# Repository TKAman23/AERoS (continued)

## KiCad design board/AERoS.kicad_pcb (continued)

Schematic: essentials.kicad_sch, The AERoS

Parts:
C29: 100n; C_0402_1005Metric; MFR. Part # CL05B104KO5NNNC; JLCPCB Part # C1525
C30, C31: 30p; C_0402_1005Metric; MFR. Part # 0402CG300J500NT; JLCPCB Part # C1570
J8: Conn_01x03_Pin; PinHeader_1x03_P2.54mm_Vertical_SMD_Pin1Left; MFR. Part # DZ254S-11-03-48; JLCPCB Part # C5160786
R25: 50k; R_0402_1005Metric; MFR. Part # RTT025002FTH; JLCPCB Part # C166559
Y1: 16M; Crystal_SMD_3225-4Pin_3.2x2.5mm; MFR. Part # X322516MMB4SI; JLCPCB Part # C112972

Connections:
+3.3V: J8.1; also elsewhere on the board
/Microcontroller/Essentials/BOOT0: R25.1; also elsewhere on the board
/Microcontroller/Essentials/HSE_IN: C30.1, Y1.1; also elsewhere on the board
/Microcontroller/Essentials/HSE_OUT: C31.1, Y1.3; also elsewhere on the board
/Microcontroller/Essentials/NRST: C29.2; also elsewhere on the board
/Microcontroller/Essentials/SW_BOOT0: J8.2, R25.2
GND: C29.1, C30.2, C31.2, J8.3, Y1.2, Y1.4; also elsewhere on the board

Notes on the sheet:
Booting Circuit
Crystal Oscillator
STM32 Functional Circuits

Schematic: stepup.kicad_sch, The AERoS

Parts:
C8, C9: 100n; C_0402_1005Metric; MFR. Part # CL05B104KO5NNNC; JLCPCB Part # C1525
C10: 22n; C_0201_0603Metric; MFR. Part # 0201X223K160NT; JLCPCB Part # C285066
C11, C15, C16: 47u; C_1812_4532Metric; MFR. Part # C4532X5R1A476MT000N; JLCPCB Part # C342615
C12: 100u; C_2220_5750Metric; MFR. Part # C5750X5R1A107MT000E; JLCPCB Part # C76692
C13: 22u; C_1210_3225Metric; MFR. Part # CL32A226KAJNNNE; JLCPCB Part # C52306
C14: 4u7; C_0805_2012Metric; MFR. Part # CL21A475KAQNNNE; JLCPCB Part # C1779
C17: 1n; C_0402_1005Metric; MFR. Part # 0402B102K500NT; JLCPCB Part # C1523
L2: 1u; 0806; MFR. Part # BDHE002016081R0MQ1; JLCPCB Part # C702824
Q5: PMOS; DFN-6-2EP_(AGM20P16AS); MFR. Part # AGM20P16AS; JLCPCB Part # C18221388
R16: 121k; R_0402_1005Metric; MFR. Part # 0402WGF1213TCE; JLCPCB Part # C11693
R17: 536k; R_0402_1005Metric; MFR. Part # 0402WGF5363TCE; JLCPCB Part # C68457
R18: 300k; R_0402_1005Metric; MFR. Part # 0402WGF3003TCE; JLCPCB Part # C25774
R19: 44k2; R_0402_1005Metric; MFR. Part # 0402WGF4422TCE; JLCPCB Part # C25895
R20: 78k7; R_0402_1005Metric; MFR. Part # 0402WGF7872TCE; JLCPCB Part # C67239
U3: TPS611781RNWR; RNW0013A; MFR. Part # TPS611781RNWR; JLCPCB Part # C2862009
U4: MCP4552T-104E/MF; DFN8_3x3MC_MCH; MFR. Part # MCP4552T-104E/MF; JLCPCB Part # C623602

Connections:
+3.3V: U4.8 (VDD); also elsewhere on the board
/Microcontroller/SERVO_ON: U3.11 (EN); also elsewhere on the board
/Power/Battery Direct/BATT_OUT: C12.1, C13.1, L2.1, U3.12 (VIN); also elsewhere on the board
/Power/Servo Power/SERVO+: C11.1, C15.1, C16.1, Q5.3 (S), R17.2; also elsewhere on the board
/Power/Servo Power/Step-Up/PREPOT: R17.1, U3.5 (FB), U4.6 (P0B)
GND: C9.1, C11.2, C12.2, C13.2, C14.2, C15.2, C16.2, C17.2, R18.2, R20.2, U3.2 (AGND), U3.6 (PGND), U4.1 (HVC/A0), U4.4 (VSS), U4.5 (P0W), U4.7 (A1), U4.9 (EP); also elsewhere on the board
unnamed: C17.1, R19.2
unnamed: C9.2, C10.1, Q5.1 (D), R16.1, U3.8 (VOUT)
unnamed: C10.2, Q5.2 (G), R16.2, U3.9 (DISDRV)
unnamed: C8.2, U3.13 (BST)
unnamed: R19.1, U3.4 (COMP)
unnamed: R18.1, U3.1 (FREQ_SYNC)
unnamed: R20.1, U3.3 (ILIMIT)
unnamed: C8.1, L2.2, U3.7 (SW)
unnamed: C14.1, U3.10 (VCC)
SCL: U4.2 (SCL); also elsewhere on the board
SDA: U4.3 (SDA); also elsewhere on the board

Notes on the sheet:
6V at 78.7k ohms
Digipot
Servo Power Step-Up
Step-Up Regulator Circuit
I2C Address: 00

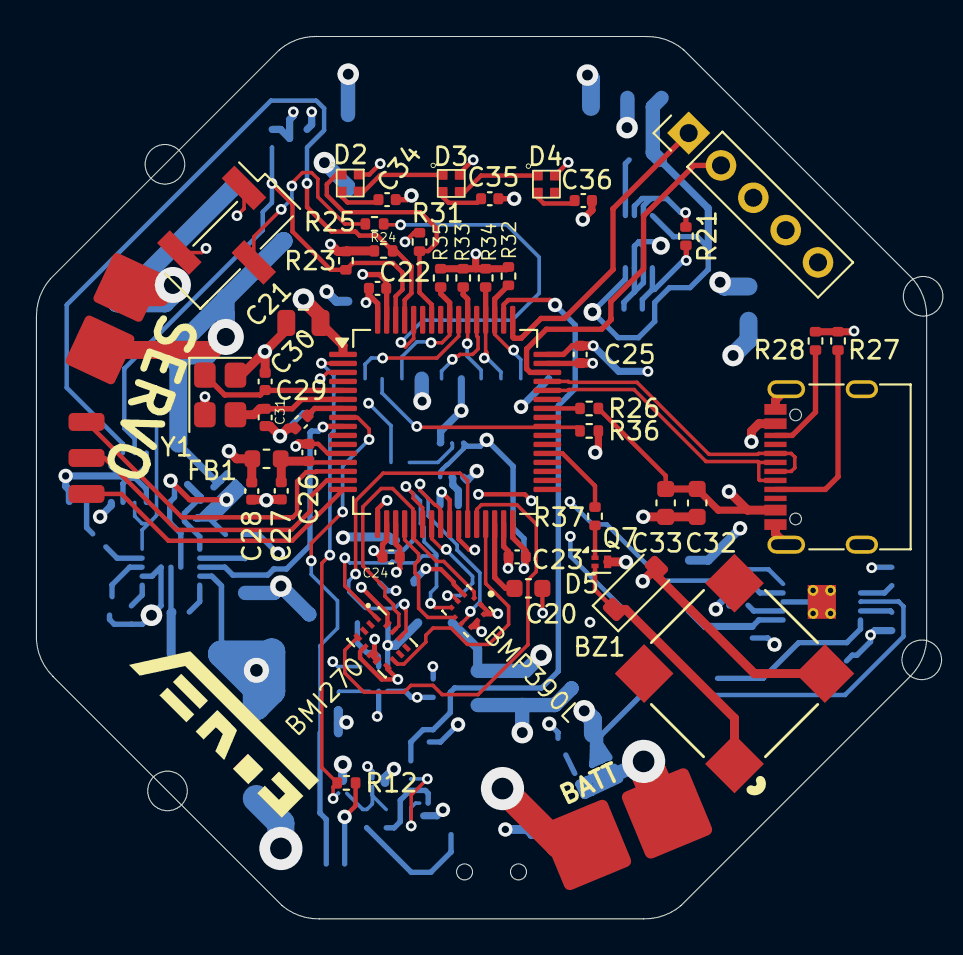
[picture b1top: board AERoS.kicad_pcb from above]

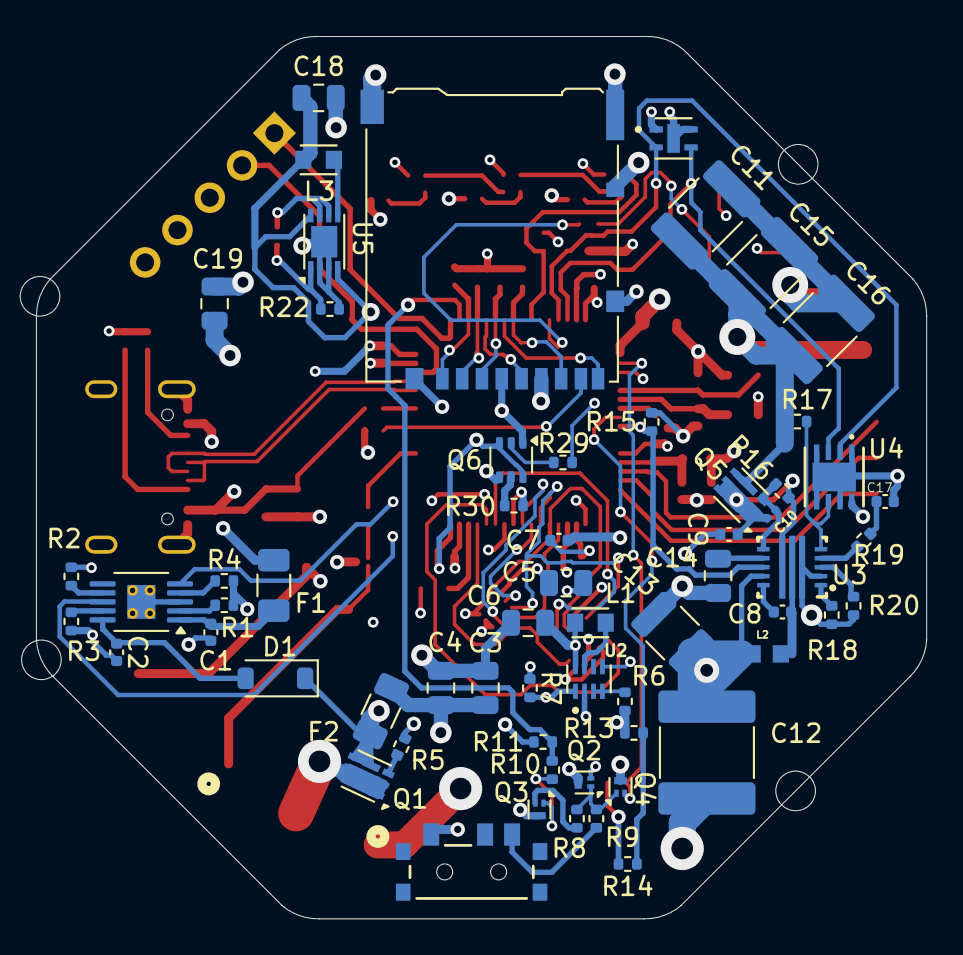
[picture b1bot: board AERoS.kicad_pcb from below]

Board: 4 copper layers, 49.5 x 49.0 mm, 118 parts (61 on the bottom side), 90 nets.

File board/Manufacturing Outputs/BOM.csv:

Comment,Designator,Footprint,JLCPCB Part #
MLT-8530,BZ1,CustomLibrary2:MLT-8530_JHE,C94599
1u,"C1,C2,C27,C28",Capacitor_SMD:C_0402_1005Metric,C14445
4u7,"C3,C4,C14,C18",Capacitor_SMD:C_0805_2012Metric,C1779
10u,"C5,C6,C19,C21",Capacitor_SMD:C_0805_2012Metric,C15850
100n,"C7,C8,C9,C22,C23,C24,C25,C29",Capacitor_SMD:C_0402_1005Metric,C1525
22n,C10,Capacitor_SMD:C_0201_0603Metric,C285066
47u,"C11,C15,C16",Capacitor_SMD:C_1812_4532Metric,C342615
100u,C12,Capacitor_SMD:C_2220_5750Metric,C76692
22u,C13,Capacitor_SMD:C_1210_3225Metric,C52306
1n,C17,Capacitor_SMD:C_0402_1005Metric,C1523
2u2,C20,Capacitor_SMD:C_0603_1608Metric,C23630
10n,C26,Capacitor_SMD:C_0402_1005Metric,C1524
30p,"C30,C31",Capacitor_SMD:C_0402_1005Metric,C1570
10u,C32,Capacitor_SMD:C_0603_1608Metric,C1691
4u7,C33,Capacitor_SMD:C_0603_1608Metric,C1705
220n,"C34,C35,C36",Capacitor_SMD:C_0402_1005Metric,C16772
SD101CW-E3-18,"D1,D5",Diode_SMD:D_SOD-123,C3313033
SK6805,"D2,D3,D4",CustomLibrary2:SK6805-EC15,C2890035
600m,F1,Fuse:Fuse_1206_3216Metric,C2154056
500m,F2,Fuse:Fuse_1206_3216Metric,C20798
GZ1608D121TF,FB1,Inductor_SMD:L_0603_1608Metric,C12391
MountingHole,"H1,H2,H3,H4",MountingHole:MountingHole_2.2mm_M2,
Conn_01x01_Pin,"J1,J2",CustomLibrary2:Pad_4x4mm,
Conn_01x01_Pin,"J3,J4",CustomLibrary2:Pad_3x3mm,
Conn_01x01_Pin,"J5,J6,J7",Connector_Wire:SolderWirePad_1x01_SMD_1x2mm,
Conn_01x03_Pin,J8,Connector_PinHeader_2.54mm:PinHeader_1x03_P2.54mm_Vertical_SMD_Pin1Left,C5160786
USB_C_Receptacle_USB2.0_14P,J9,Connector_USB:USB_C_Receptacle_G-Switch_GT-USB-7010ASV,C2988369
Conn_01x05_Pin,J10,Connector_PinHeader_2.54mm:PinHeader_1x05_P2.54mm_Vertical,
SD Card Hirose DM3AT,J11,Connector_Card:microSD_HC_Hirose_DM3AT-SF-PEJM5,C114218
2u2,"L1,L3",CustomLibrary2:IND_LQH2MPZ2R2MGRL,C2042050
1u,L2,CustomLibrary2:0806,C702824
PMOS,"Q1,Q5",CustomLibrary2:DFN-6-2EP_(AGM20P16AS),C18221388
NMOS,"Q2,Q3,Q4,Q7",CustomLibrary2:DFN-3(0.6x1),C20605534
NMOS,Q6,Package_TO_SOT_SMD:SOT-363_SC-70-6,C15215
1k,"R1,R5,R8,R9,R23,R24,R29,R30,R32,R33,R34,R35,R36",Resistor_SMD:R_0402_1005Metric,C11702
10k,"R2,R3,R31",Resistor_SMD:R_0402_1005Metric,C25744
1k5,R4,Resistor_SMD:R_0402_1005Metric,C25867
100k,"R6,R11,R12,R13,R15,R26",Resistor_SMD:R_0402_1005Metric,C25741
267k,R7,Resistor_SMD:R_0402_1005Metric,C270622
100,R10,Resistor_SMD:R_0402_1005Metric,C25076
365k,R14,Resistor_SMD:R_0402_1005Metric,C27006
121k,R16,Resistor_SMD:R_0402_1005Metric,C11693
536k,R17,Resistor_SMD:R_0402_1005Metric,C68457
300k,R18,Resistor_SMD:R_0402_1005Metric,C25774
44k2,R19,Resistor_SMD:R_0402_1005Metric,C25895
78k7,R20,Resistor_SMD:R_0402_1005Metric,C67239
976k,R21,Resistor_SMD:R_0402_1005Metric,C25802
562k,R22,Resistor_SMD:R_0402_1005Metric,C48838
50k,R25,Resistor_SMD:R_0402_1005Metric,C166559
5k1,"R27,R28",Resistor_SMD:R_0402_1005Metric,C25905
470,R37,Resistor_SMD:R_0402_1005Metric,C25117
SW_SPDT,SW1,CustomLibrary2:MK-12C02-G020_GSW,C963206
BQ24090DGQ,U1,Package_SO:HVSSOP-10-1EP_3x3mm_P0.5mm_EP1.57x1.88mm_ThermalVias,C43306
TPS62840DLCR,U2,CustomLibrary2:SON50P200X150X100-8N,C2071859
TPS611781RNWR,U3,Custom_Library:RNW0013A,C2862009
MCP4552T-104E/MF,U4,CustomLibrary2:DFN8_3x3MC_MCH,C623602
MCP1640x-xMC,U5,Package_DFN_QFN:DFN-8-1EP_3x2mm_P0.5mm_EP1.75x1.45mm,C623037
STM32F411RET6,U6,Package_QFP:LQFP-64_10x10mm_P0.5mm,C94355
BMI270,U7,Custom_Library:XDCR_BMI270,C2836813
BMP390L,U8,Custom_Library:XDCR_BMP390L,C2684802
SHTC3,U9,Custom_Library:SON100P200X200X80-5N,C194656
16M,Y1,Crystal:Crystal_SMD_3225-4Pin_3.2x2.5mm,C5452684

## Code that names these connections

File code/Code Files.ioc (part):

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Mcu.Name=STM32F411R(C-E)Tx
Mcu.Package=LQFP64
Mcu.UserName=STM32F411RETx
PA0-WKUP.GPIOParameters=GPIO_Label
PA0-WKUP.GPIO_Label=SERVO1
PA0-WKUP.Signal=S_TIM2_CH1_ETR
PA1.GPIOParameters=GPIO_Label
PA1.GPIO_Label=SERVO2
PA1.Signal=S_TIM2_CH2
PA10.Signal=GPIO_Analog
PA11.GPIOParameters=GPIO_Label
PA11.GPIO_Label=USB_D-
PA11.Mode=Device_Only
PA11.Signal=USB_OTG_FS_DM
PA12.GPIOParameters=GPIO_Label
PA12.GPIO_Label=USB_D+
PA12.Mode=Device_Only
PA12.Signal=USB_OTG_FS_DP
PA13.GPIOParameters=GPIO_Label
PA13.GPIO_Label=SW_DIO
PA13.Mode=Serial_Wire
PA13.Signal=SYS_JTMS-SWDIO
PA14.GPIOParameters=GPIO_Label
PA14.GPIO_Label=SW_CLK
PA14.Mode=Serial_Wire
PA14.Signal=SYS_JTCK-SWCLK
PA15.GPIOParameters=GPIO_Label
PA15.GPIO_Label=KEEP_ON
PA15.Signal=GPIO_Output
PA2.GPIOParameters=GPIO_Label
PA2.GPIO_Label=SERVO3
PA2.Signal=S_TIM2_CH3
PA3.Signal=GPIO_Analog
PA4.GPIOParameters=GPIO_Label
PA4.GPIO_Label=BMP_CS
PA4.Signal=GPIO_Output
PA5.GPIOParameters=GPIO_Label
PA5.GPIO_Label=CLK
PA5.Mode=Full_Duplex_Master
PA5.Signal=SPI1_SCK
PA6.GPIOParameters=GPIO_Label
PA6.GPIO_Label=MISO
PA6.Mode=Full_Duplex_Master
PA6.Signal=SPI1_MISO
PA7.GPIOParameters=GPIO_Label
PA7.GPIO_Label=MOSI
PA7.Mode=Full_Duplex_Master
PA7.Signal=SPI1_MOSI
PA8.Signal=GPIO_Analog
PA9.GPIOParameters=GPIO_Label
PA9.GPIO_Label=USB_SENSE
PA9.Mode=Activate_VBUS
PA9.Signal=USB_OTG_FS_VBUS
PB0.Signal=GPIO_Analog
PB1.GPIOParameters=GPIO_Label
PB1.GPIO_Label=IMU_CS
PB1.Signal=GPIO_Output
PB10.GPIOParameters=GPIO_Label
PB10.GPIO_Label=IMU_INT2
PB10.Signal=GPXTI10
PB12.Signal=GPIO_Analog
PB13.Signal=GPIO_Analog
PB14.Signal=GPIO_Analog
PB15.Signal=GPIO_Analog
PB2.GPIOParameters=GPIO_Label
PB2.GPIO_Label=IMU_INT1
PB2.Signal=GPXTI2
PB3.GPIOParameters=GPIO_Label
PB3.GPIO_Label=SD_SW
PB3.Signal=GPXTI3
PB4.GPIOParameters=GPIO_Label
PB4.GPIO_Label=DAT0
PB4.Mode=SD_4_bits_Wide_bus
PB4.Signal=SDIO_D0
PB5.GPIOParameters=GPIO_Label
PB5.GPIO_Label=CHG
PB5.Signal=GPXTI5
PB6.GPIOParameters=GPIO_Label
PB6.GPIO_Label=LED
PB6.Signal=S_TIM4_CH1
PB7.GPIOParameters=GPIO_Label
PB7.GPIO_Label=PG
PB7.Signal=GPXTI7
PB8.GPIOParameters=GPIO_Label
PB8.GPIO_Label=SCL
PB8.Mode=I2C
PB8.Signal=I2C1_SCL
PB9.GPIOParameters=GPIO_Label
PB9.GPIO_Label=SDA
PB9.Mode=I2C
PB9.Signal=I2C1_SDA
PC0.GPIOParameters=GPIO_Label
PC0.GPIO_Label=VSENSE
PC0.Signal=ADCx_IN10
PC1.GPIOParameters=GPIO_Label
PC1.GPIO_Label=SERVO_ON
PC1.Signal=GPIO_Output
PC10.GPIOParameters=GPIO_Label
PC10.GPIO_Label=DAT2
PC10.Mode=SD_4_bits_Wide_bus
PC10.Signal=SDIO_D2
PC11.GPIOParameters=GPIO_Label
PC11.GPIO_Label=DAT3
PC11.Mode=SD_4_bits_Wide_bus
PC11.Signal=SDIO_D3
PC12.GPIOParameters=GPIO_Label
PC12.GPIO_Label=SD_CLK
PC12.Mode=SD_4_bits_Wide_bus
PC12.Signal=SDIO_CK
PC13-ANTI_TAMP.GPIOParameters=GPIO_Label
PC13-ANTI_TAMP.GPIO_Label=POWER_TOGGLE
PC13-ANTI_TAMP.Signal=GPXTI13
PC14-OSC32_IN.GPIOParameters=GPIO_Label
PC14-OSC32_IN.GPIO_Label=SD_ON
PC14-OSC32_IN.Signal=GPIO_Output
PC15-OSC32_OUT.Signal=GPIO_Analog
PC2.Signal=GPIO_Analog
PC3.Signal=GPIO_Analog
PC4.GPIOParameters=GPIO_Label
PC4.GPIO_Label=BMP_INT
PC4.Signal=GPXTI4
PC5.GPIOParameters=GPIO_Label
PC5.GPIO_Label=SENSE_ON
PC5.Signal=GPIO_Output
PC6.GPIOParameters=GPIO_PuPd,GPIO_Label
PC6.GPIO_Label=BUZZ
PC6.GPIO_PuPd=GPIO_PULLDOWN
PC6.Signal=S_TIM3_CH1
PC7.Signal=GPIO_Analog
PC8.Signal=GPIO_Analog
PC9.GPIOParameters=GPIO_Label
PC9.GPIO_Label=DAT1
PC9.Mode=SD_4_bits_Wide_bus
PC9.Signal=SDIO_D1
PD2.GPIOParameters=GPIO_Label
PD2.GPIO_Label=SD_CMD
PD2.Mode=SD_4_bits_Wide_bus
PD2.Signal=SDIO_CMD
PH0\ -\ OSC_IN.GPIOParameters=GPIO_Label
PH0\ -\ OSC_IN.GPIO_Label=HSE_IN
PH0\ -\ OSC_IN.Mode=HSE-External-Oscillator
PH0\ -\ OSC_IN.Signal=RCC_OSC_IN
PH1\ -\ OSC_OUT.GPIOParameters=GPIO_Label
PH1\ -\ OSC_OUT.GPIO_Label=HSE_OUT
PH1\ -\ OSC_OUT.Mode=HSE-External-Oscillator
PH1\ -\ OSC_OUT.Signal=RCC_OSC_OUT
RCC.HSE_VALUE=16000000
RCC.SYSCLKFreq_VALUE=96000000
RCC.SYSCLKSource=RCC_SYSCLKSOURCE_PLLCLK
board=custom
